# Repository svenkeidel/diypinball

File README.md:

# DiyPinball
The **DiyPinball** project (working title, for lack of a better name).

## Arduino
The Arduino sketch is in the `arduino` folder. We're using an Arduino Uno.

## Boards
The board layouts and schematics are in the `boards` folder. We use KiCAD for the boards.

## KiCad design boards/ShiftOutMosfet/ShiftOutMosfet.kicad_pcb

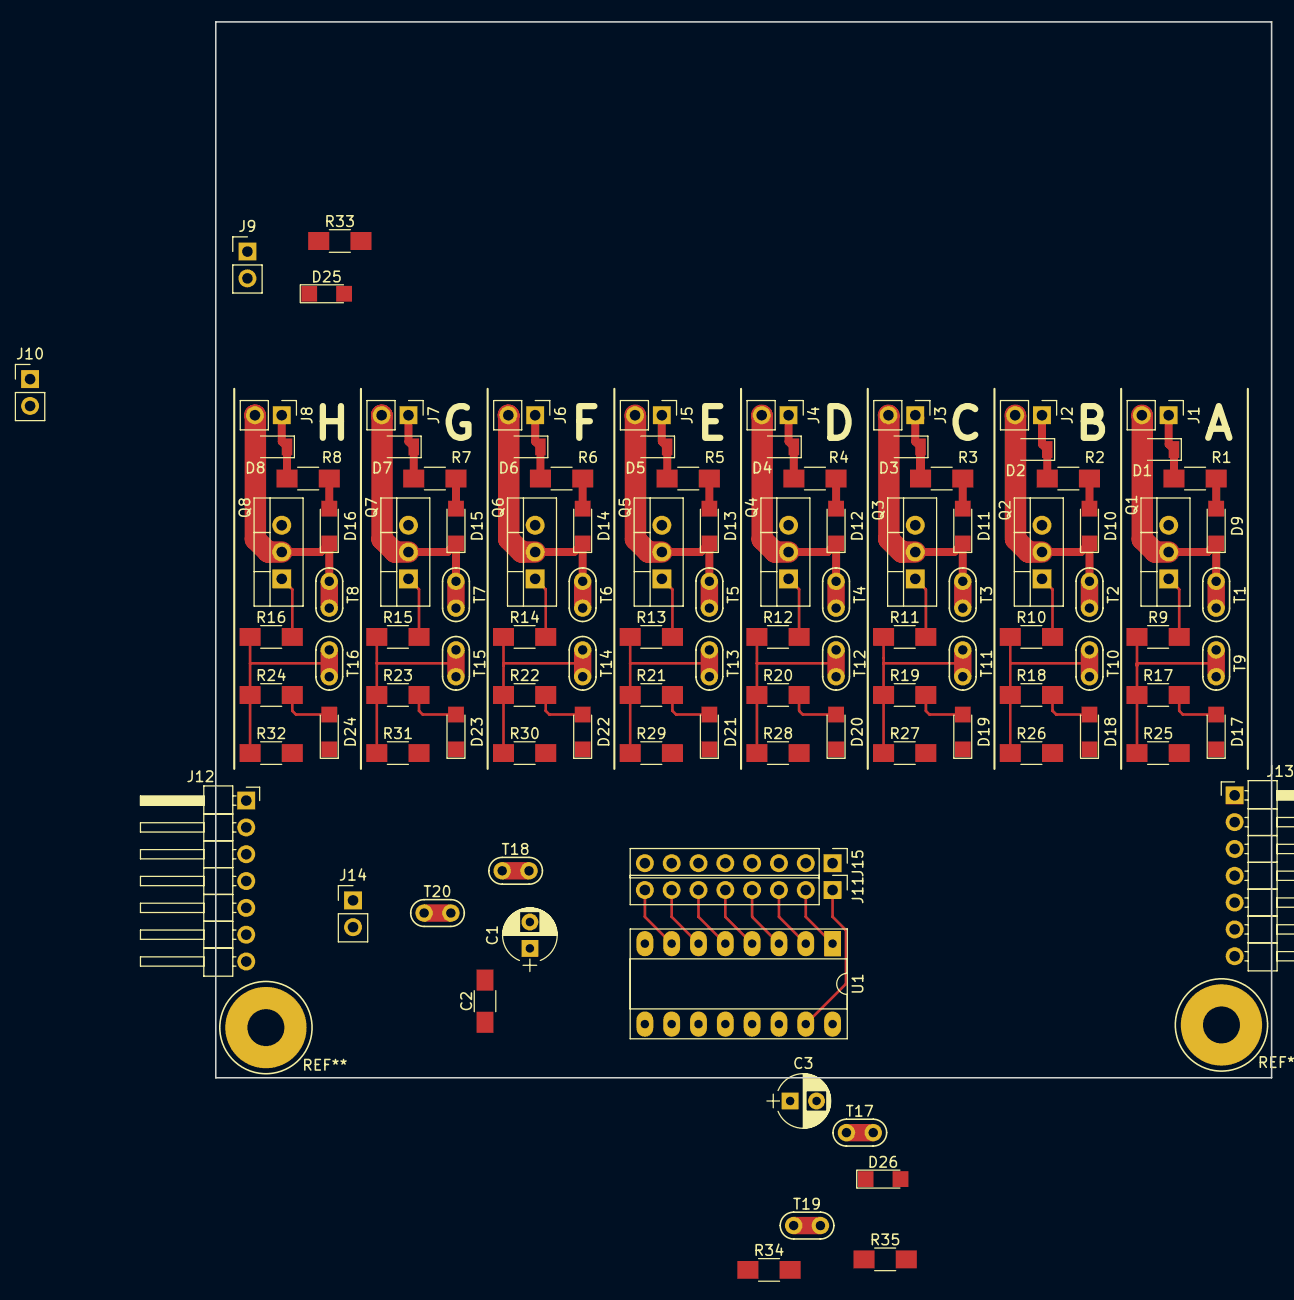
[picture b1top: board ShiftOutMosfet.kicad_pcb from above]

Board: 2 copper layers, 100.0 x 100.0 mm, 108 parts (0 on the bottom side), 60 nets.

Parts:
C1: 100U; CP_Radial_D5.0mm_P2.50mm
C2: 0.1U; C_1206_HandSoldering
C3: C; CP_Radial_D5.0mm_P2.50mm
D1, D2, D3, D4, D5, D6, D7, D8: 1N4148; D_1206
D9, D10, D11, D12, D13, D14, D15, D16, D17, D18, D19, D20, D21, D22, D23, D24, D25, D26: 2mA 1.9V; LED_1206
J1: CONN_A; Pin_Header_Straight_1x02_Pitch2.54mm
J2: CONN_B; Pin_Header_Straight_1x02_Pitch2.54mm
J3: CONN_C; Pin_Header_Straight_1x02_Pitch2.54mm
J4: CONN_D; Pin_Header_Straight_1x02_Pitch2.54mm
J5: CONN_E; Pin_Header_Straight_1x02_Pitch2.54mm
J6: CONN_F; Pin_Header_Straight_1x02_Pitch2.54mm
J7: CONN_G; Pin_Header_Straight_1x02_Pitch2.54mm
J8: CONN_H; Pin_Header_Straight_1x02_Pitch2.54mm
J9: CONN_VDD_IN; Pin_Header_Straight_1x02_Pitch2.54mm
J10: CONN_VDD_OUT; Pin_Header_Straight_1x02_Pitch2.54mm
J11: CONN_SIG_IN; Pin_Header_Straight_1x08_Pitch2.54mm
J12: CONN_LOGIC_IN; Pin_Header_Angled_1x07_Pitch2.54mm_Mirrored
J13: CONN_LOGIC_OUT; Pin_Header_Angled_1x07_Pitch2.54mm
J14: CONN_GNDS; Pin_Header_Straight_1x02_Pitch2.54mm
J15: CONN_SIG_OUT; Pin_Header_Straight_1x08_Pitch2.54mm
Q1, Q2, Q3, Q4, Q5, Q6, Q7, Q8: IRL540N; TO-220_Vertical
R1, R2, R3, R4, R5, R6, R7, R8: 33K; R_1206_HandSoldering
R9, R10, R11, R12, R13, R14, R15, R16: 470K; R_1206_HandSoldering
R17, R18, R19, R20, R21, R22, R23, R24: 1K8; R_1206_HandSoldering
R25, R26, R27, R28, R29, R30, R31, R32, R34: 10K; R_1206_HandSoldering
R33, R35: 1K6; R_1206_HandSoldering
T1, T2, T3, T4, T5, T6, T7, T8, T9, T10, T11, T12, T13, T14, T15, T16, T17, T18, T19, T20: TEST_LOOP
U1: 74HC595; DIP-16_W7.62mm_Socket_LongPads

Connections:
+5V: C1.1, C2.1, C3.1, J12.1, J13.1, R34.1, R35.2, T19.1, U1.16
/A: J11.1, U1.15
/B: J11.2, U1.1
/C: J11.3, U1.2
/D: J11.4, U1.3
/E: J11.5, U1.4
/F: J11.6, U1.5
/G: J11.7, U1.6
/H: J11.8, U1.7
/LATCH_CLK: J12.6, J13.6, U1.12
/SER_CLK: J12.5, J13.5, U1.11
/SER_IN: J12.7, U1.14
/SER_OUT: J13.7, U1.9
/SIG_A: J15.1, R9.1, R17.1, R25.1, T9.1
/SIG_B: J15.2, R10.1, R18.1, R26.1, T10.1
/SIG_C: J15.3, R11.1, R19.1, R27.1, T11.1
/SIG_D: J15.4, R12.1, R20.1, R28.1, T12.1
/SIG_E: J15.5, R13.1, R21.1, R29.1, T13.1
/SIG_F: J15.6, R14.1, R22.1, R30.1, T14.1
/SIG_G: J15.7, R15.1, R23.1, R31.1, T15.1
/SIG_H: J15.8, R16.1, R24.1, R32.1, T16.1
/~OE: J12.4, J13.4, R34.2, U1.13
/~RESET: J12.3, J13.3, U1.10
GND: C1.2, C2.2, C3.2, D17.1, D18.1, D19.1, D20.1, D21.1, D22.1, D23.1, D24.1, D26.1, J12.2, J13.2, J14.2, R25.2, R26.2, R27.2, R28.2, R29.2, R30.2, R31.2, R32.2, T20.1, U1.8
GNDPWR: D25.1, J9.2, J10.2, J14.1, Q1.3, Q2.3, Q3.3, Q4.3, Q5.3, Q6.3, Q7.3, Q8.3, T17.1
unnamed: D1.2, D9.1, J1.2, Q1.2, T1.1
unnamed: D9.2, R1.1
unnamed: D2.2, D10.1, J2.2, Q2.2, T2.1
unnamed: D10.2, R2.1
unnamed: D3.2, D11.1, J3.2, Q3.2, T3.1
unnamed: D11.2, R3.1
unnamed: D4.2, D12.1, J4.2, Q4.2, T4.1
unnamed: D12.2, R4.1
unnamed: D5.2, D13.1, J5.2, Q5.2, T5.1
unnamed: D13.2, R5.1
unnamed: D6.2, D14.1, J6.2, Q6.2, T6.1
unnamed: D14.2, R6.1
unnamed: D7.2, D15.1, J7.2, Q7.2, T7.1
unnamed: D15.2, R7.1
unnamed: D8.2, D16.1, J8.2, Q8.2, T8.1
unnamed: D16.2, R8.1
unnamed: D17.2, R17.2
unnamed: D18.2, R18.2
unnamed: D19.2, R19.2
unnamed: D20.2, R20.2
unnamed: D21.2, R21.2
unnamed: D22.2, R22.2
unnamed: D23.2, R23.2
unnamed: D24.2, R24.2
unnamed: D25.2, R33.2
unnamed: D26.2, R35.1
unnamed: Q1.1, R9.2
unnamed: Q2.1, R10.2
unnamed: Q3.1, R11.2
unnamed: Q4.1, R12.2
unnamed: Q5.1, R13.2
unnamed: Q6.1, R14.2
unnamed: Q7.1, R15.2
unnamed: Q8.1, R16.2
VDD: D1.1, D2.1, D3.1, D4.1, D5.1, D6.1, D7.1, D8.1, J1.1, J2.1, J3.1, J4.1, J5.1, J6.1, J7.1, J8.1, J9.1, J10.1, R1.2, R2.2, R3.2, R4.2, R5.2, R6.2, R7.2, R8.2, R33.1, T18.1

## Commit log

2017-02-14 Add Pinball Arduino sketch
2017-02-22 Add slingshot/pop bumber handling and trough
2017-03-02 Add shift register for outputs
2017-03-08 Add Shift board
2017-03-10 Add shift register for inputs
2017-03-10 Start working on PCB design
2017-03-17 Enabled plunger function. Added another pin pair that behaves like slingshot.
2017-03-18 Shift mosfet board
2017-03-21 add score and code to update display
